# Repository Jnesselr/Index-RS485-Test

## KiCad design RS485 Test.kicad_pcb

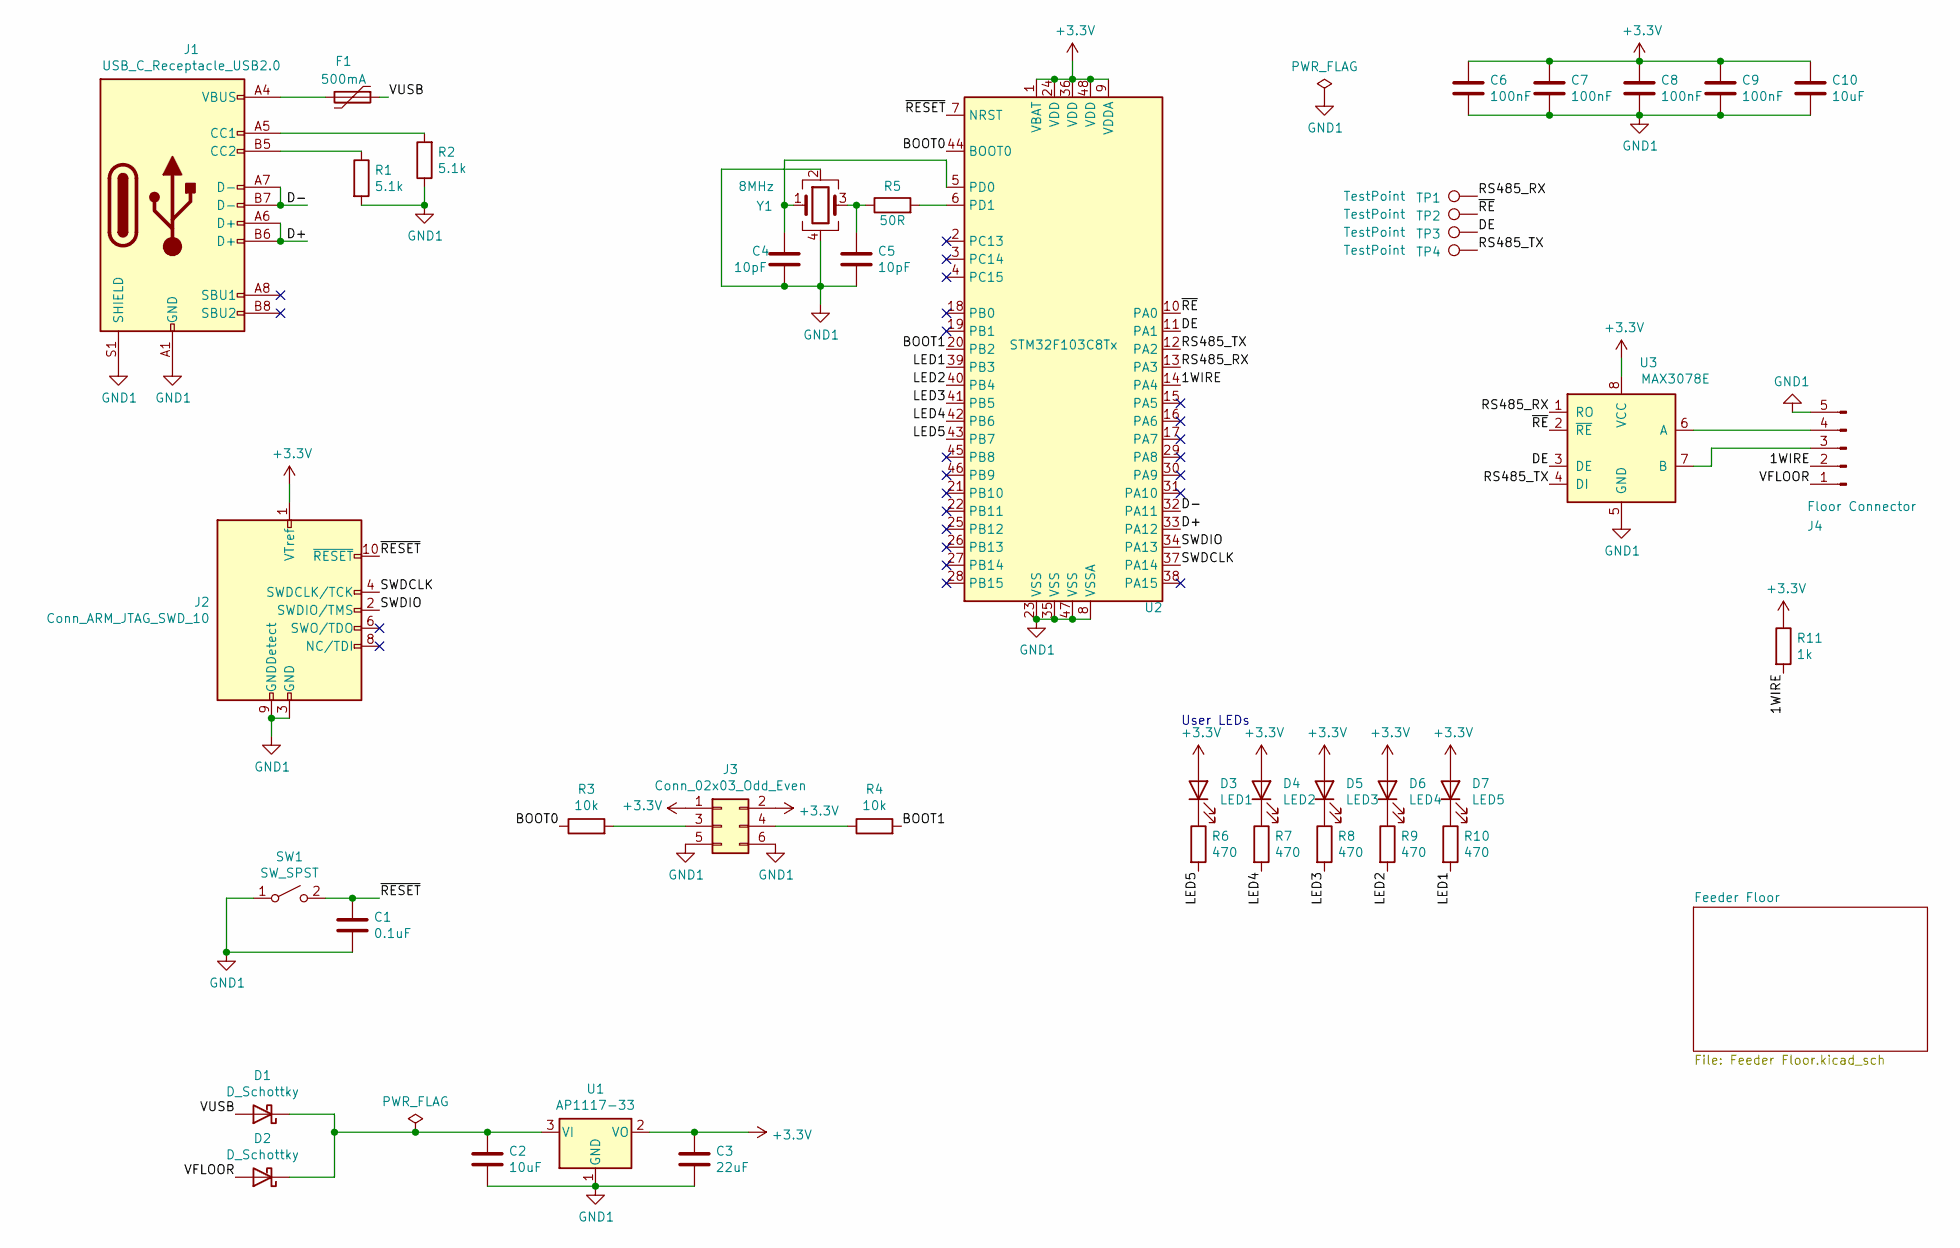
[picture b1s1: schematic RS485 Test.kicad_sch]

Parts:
C1: 0.1uF; C_0603_1608Metric_Pad1.08x0.95mm_HandSolder
C2, C10: 10uF; C_0603_1608Metric_Pad1.08x0.95mm_HandSolder
C3: 22uF; C_0603_1608Metric_Pad1.08x0.95mm_HandSolder
C4, C5: 10pF; C_0603_1608Metric_Pad1.08x0.95mm_HandSolder
C6, C7, C8, C9: 100nF; C_0603_1608Metric_Pad1.08x0.95mm_HandSolder
D1, D2: D_Schottky; D_0603_1608Metric_Pad1.05x0.95mm_HandSolder
D3: LED1; LED_0603_1608Metric_Pad1.05x0.95mm_HandSolder
D4: LED2; LED_0603_1608Metric_Pad1.05x0.95mm_HandSolder
D5: LED3; LED_0603_1608Metric_Pad1.05x0.95mm_HandSolder
D6: LED4; LED_0603_1608Metric_Pad1.05x0.95mm_HandSolder
D7: LED5; LED_0603_1608Metric_Pad1.05x0.95mm_HandSolder
F1: 500mA; MF-MSMF050-2; Part Number MF-MSMF050-2
J1: USB_C_Receptacle_USB2.0; USB_C_Receptacle_HRO_TYPE-C-31-M-12
J2: Conn_ARM_JTAG_SWD_10; PinHeader_2x05_P1.00mm_Vertical
J3: Conn_02x03_Odd_Even; PinHeader_2x03_P2.54mm_Vertical
J4: Floor Connector; PinHeader_1x05_P2.54mm_Horizontal
R1, R2: 5.1k; R_0603_1608Metric_Pad0.98x0.95mm_HandSolder
R3, R4: 10k; R_0603_1608Metric_Pad0.98x0.95mm_HandSolder
R5: 50R; R_0603_1608Metric_Pad0.98x0.95mm_HandSolder
R6, R7, R8, R9, R10: 470; R_0603_1608Metric_Pad0.98x0.95mm_HandSolder
R11: 1k; R_0603_1608Metric_Pad0.98x0.95mm_HandSolder
SW1: SW_SPST; SW_SPST_FSMSM
TP1, TP2, TP3, TP4: TestPoint; TestPoint_Pad_D2.0mm
U1: AP1117-33; SOT-223-3_TabPin2
U2: STM32F103C8Tx; LQFP-48_7x7mm_P0.5mm
U3: MAX3078E; SOIC-8_3.9x4.9mm_P1.27mm
Y1: 8MHz; Crystal_SMD_3225-4Pin_3.2x2.5mm_HandSoldering

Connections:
+3V3: C3.1, C6.1, C7.1, C8.1, C9.1, C10.1, D3.2 (A), D4.2 (A), D5.2 (A), D6.2 (A), D7.2 (A), J2.1 (VTref), J3.1, J3.2, R11.1, U1.2 (VO), U2.1 (VBAT), U2.9 (VDDA), U2.24 (VDD), U2.36 (VDD), U2.48 (VDD), U3.8 (VCC)
/1WIRE: J4.2, R11.2, U2.14 (PA4)
/BOOT0: R3.1, U2.44 (BOOT0)
/BOOT1: R4.2, U2.20 (PB2)
/D+: J1.A6 (D+), J1.B6 (D+), U2.33 (PA12)
/D-: J1.A7 (D-), J1.B7 (D-), U2.32 (PA11)
/DE: TP3.1, U2.11 (PA1), U3.3 (DE)
/LED1: R10.2, U2.39 (PB3)
/LED2: R9.2, U2.40 (PB4)
/LED3: R8.2, U2.41 (PB5)
/LED4: R7.2, U2.42 (PB6)
/LED5: R6.2, U2.43 (PB7)
/RS485_RX: TP1.1, U2.13 (PA3), U3.1 (RO)
/RS485_TX: TP4.1, U2.12 (PA2), U3.4 (DI)
/SWDCLK: J2.4 (SWDCLK/TCK), U2.37 (PA14)
/SWDIO: J2.2 (SWDIO/TMS), U2.34 (PA13)
/VFLOOR: D2.2 (A), J4.1
/VUSB: D1.2 (A), F1.1
/~RE: TP2.1, U2.10 (PA0), U3.2 (~RE~)
/~RESET: C1.1, J2.10 (~RESET~), SW1.2 (B), U2.7 (NRST)
GND1: C1.2, C2.2, C3.2, C4.2, C5.2, C6.2, C7.2, C8.2, C9.2, C10.2, J1.A1 (GND), J1.A12 (GND), J1.B1 (GND), J1.B12 (GND), J1.S1 (SHIELD), J2.3 (GND), J2.5 (GND), J2.9 (GNDDetect), J3.5, J3.6, J4.5, R1.2, R2.1, SW1.1 (A), U1.1 (GND), U2.8 (VSSA), U2.23 (VSS), U2.35 (VSS), U2.47 (VSS), U3.5 (GND), Y1.2, Y1.4
unnamed: C2.1, D1.1 (K), D2.1 (K), U1.3 (VI)
unnamed: C4.1, U2.5 (PD0), Y1.1
unnamed: C5.1, R5.1, Y1.3
unnamed: D3.1 (K), R6.1
unnamed: D4.1 (K), R7.1
unnamed: D5.1 (K), R8.1
unnamed: D6.1 (K), R9.1
unnamed: D7.1 (K), R10.1
unnamed: F1.2, J1.A4 (VBUS), J1.A9 (VBUS), J1.B4 (VBUS), J1.B9 (VBUS)
unnamed: J1.A5 (CC1), R2.2
unnamed: J1.B5 (CC2), R1.1
unnamed: J3.3, R3.2
unnamed: J3.4, R4.1
unnamed: J4.3, U3.7 (B)
unnamed: J4.4, U3.6 (A)
unnamed: R5.2, U2.6 (PD1)
no_connect_(J1-PadA8): J1.A8 (SBU1)
no_connect_(J1-PadB8): J1.B8 (SBU2)
no_connect_(J2-Pad6): J2.6 (SWO/TDO)
no_connect_(J2-Pad7): J2.7 (KEY)
no_connect_(J2-Pad8): J2.8 (NC/TDI)
no_connect_(U2-Pad2): U2.2 (PC13)
no_connect_(U2-Pad3): U2.3 (PC14)
no_connect_(U2-Pad4): U2.4 (PC15)
no_connect_(U2-Pad15): U2.15 (PA5)
no_connect_(U2-Pad16): U2.16 (PA6)
no_connect_(U2-Pad17): U2.17 (PA7)
no_connect_(U2-Pad18): U2.18 (PB0)
no_connect_(U2-Pad19): U2.19 (PB1)
no_connect_(U2-Pad21): U2.21 (PB10)
no_connect_(U2-Pad22): U2.22 (PB11)
no_connect_(U2-Pad25): U2.25 (PB12)
no_connect_(U2-Pad26): U2.26 (PB13)
no_connect_(U2-Pad27): U2.27 (PB14)
no_connect_(U2-Pad28): U2.28 (PB15)
no_connect_(U2-Pad29): U2.29 (PA8)
no_connect_(U2-Pad30): U2.30 (PA9)
no_connect_(U2-Pad31): U2.31 (PA10)
no_connect_(U2-Pad38): U2.38 (PA15)
no_connect_(U2-Pad45): U2.45 (PB8)
no_connect_(U2-Pad46): U2.46 (PB9)

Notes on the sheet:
User LEDs

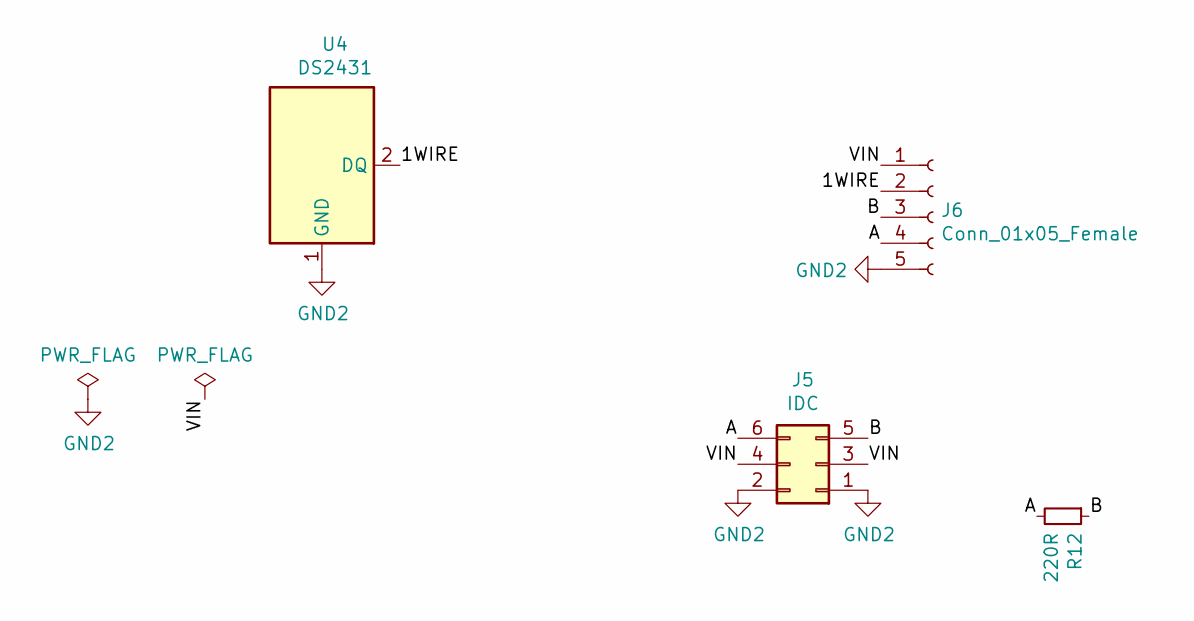
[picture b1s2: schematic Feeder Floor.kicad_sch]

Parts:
J5: IDC; IDC-Header_2x03_P2.54mm_Vertical
J6: Conn_01x05_Female; PinSocket_1x05_P2.54mm_Vertical
R12: 220R; R_0603_1608Metric_Pad0.98x0.95mm_HandSolder
U4: DS2431; TSOC-6_3.76x3.94mm_P1.27mm

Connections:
/Feeder Floor/1WIRE: J6.2, U4.2 (DQ)
/Feeder Floor/A: J5.6, J6.4, R12.2
/Feeder Floor/B: J5.5, J6.3, R12.1
/Feeder Floor/VIN: J5.3, J5.4, J6.1
GND2: J5.1, J5.2, J6.5, U4.1 (GND)
no_connect_(U4-Pad3): U4.3 (NC)
no_connect_(U4-Pad4): U4.4 (NC)
no_connect_(U4-Pad5): U4.5 (NC)
no_connect_(U4-Pad6): U4.6 (NC)

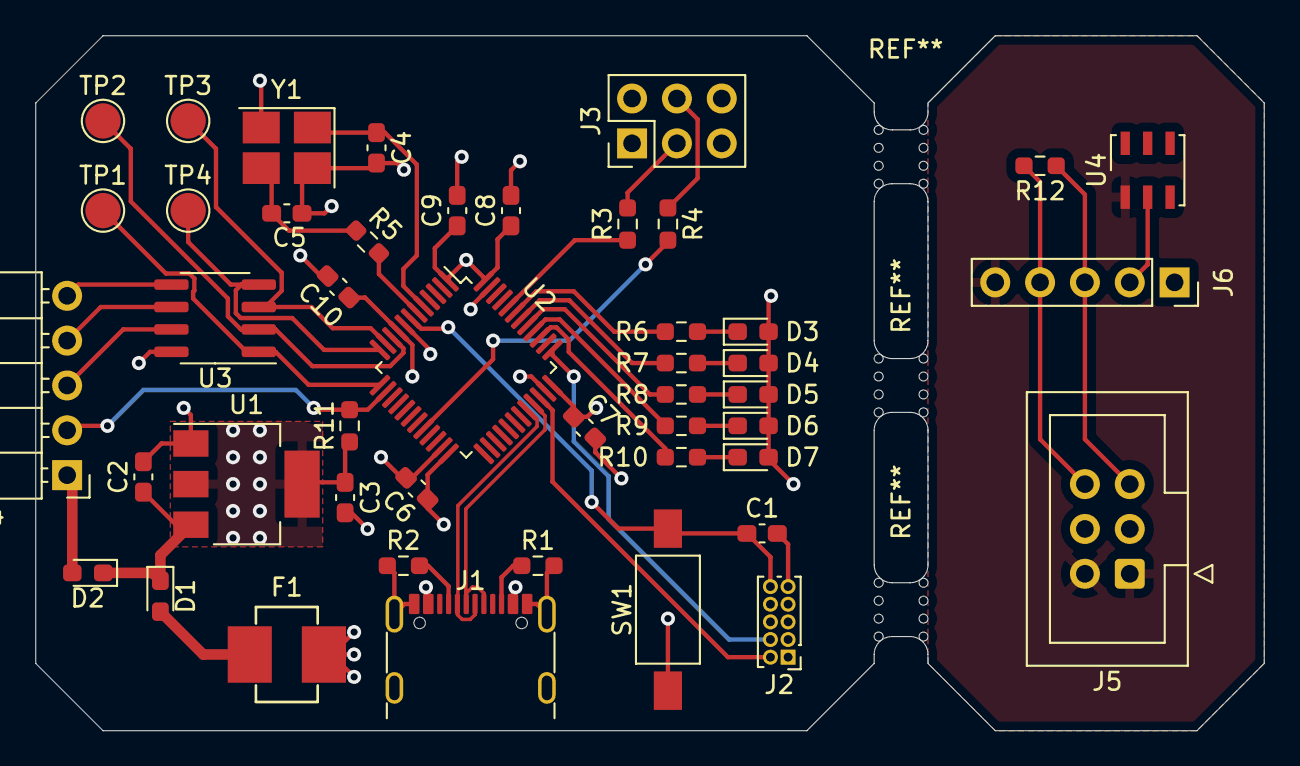
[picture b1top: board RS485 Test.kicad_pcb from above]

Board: 4 copper layers, 69.6 x 39.4 mm, 46 parts (0 on the bottom side), 42 nets.

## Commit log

2021-01-21 Removed backups
2021-01-21 Fixing DRC issues
